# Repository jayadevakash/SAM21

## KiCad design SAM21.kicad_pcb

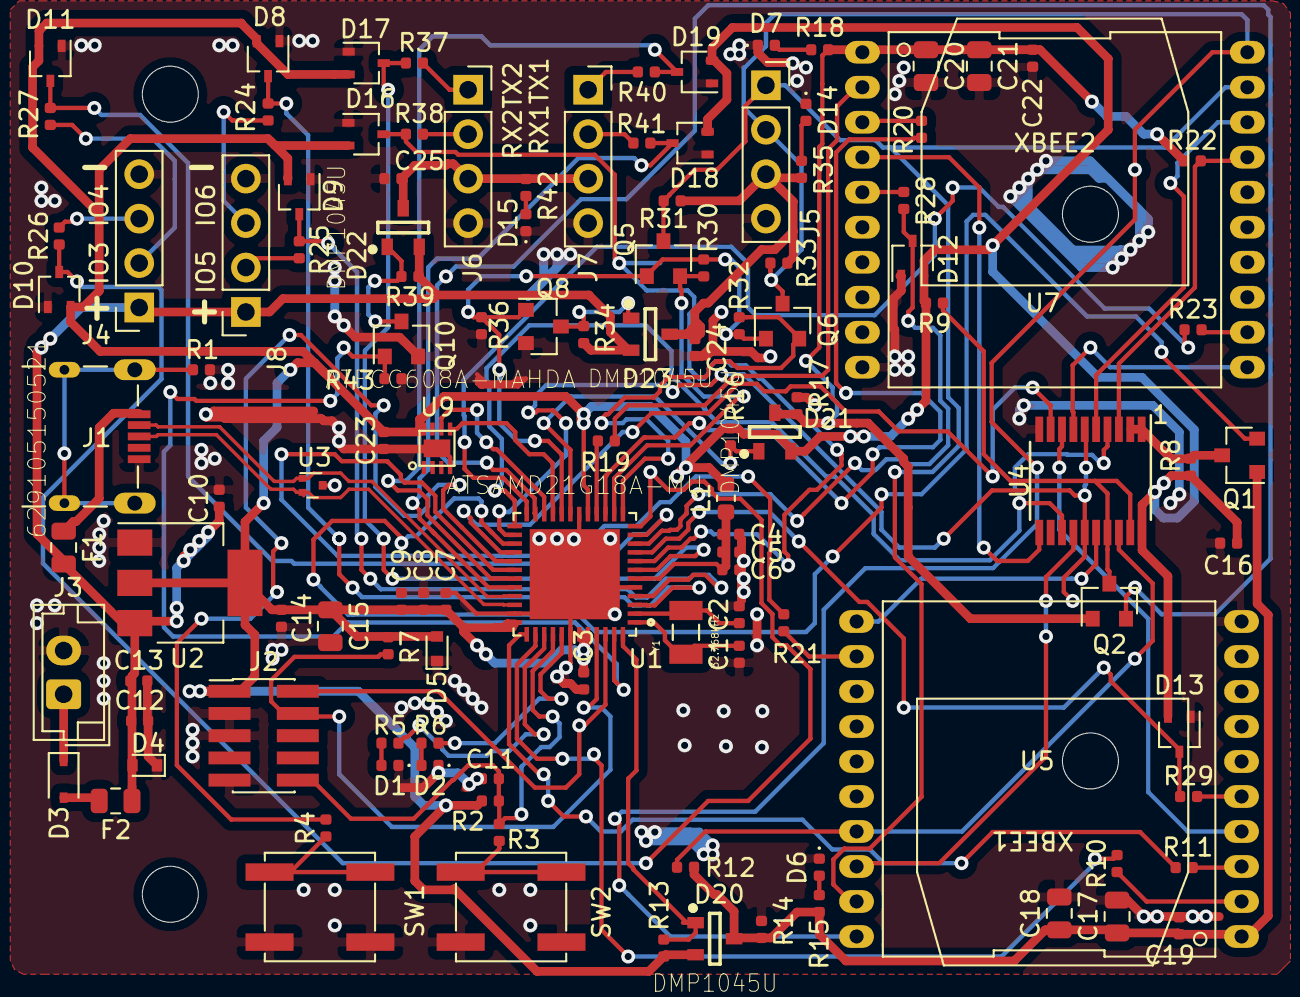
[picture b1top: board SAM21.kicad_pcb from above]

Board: 2 copper layers, 122 parts (0 on the bottom side), 89 nets.

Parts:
C1, C2: 12pF; C_0402_1005Metric
C3, C4, C5, C19, C22, C24, C25: 2u2F; C_0402_1005Metric
C6, C7, C8, C9, C10, C11, C12, C13, C14, C16, C23: 100nF; C_0402_1005Metric
C15, C17, C18, C20, C21: 22uF; C_0805_2012Metric
D1, D2, D6, D7, D14, D15: LED; LED_0402_1005Metric
D3: BAS3010; D_SOD-323
D4: ESD5Z5.0T1G; D_SOD-523
D5: ESD5Z3.3T1G; D_SOD-523
D8, D9, D10, D11, D12, D13, D16, D17, D18, D19: D_BAT30S; SOT-323_SC-70
D20, D21, D22, D23: DMP1045U; SOT92P240X110-3N
F1, F2: 0.5A; Fuse_0805_2012Metric
H1, H2, H3, H4: MountingHole; MountingHole_3.2mm_M3
J1: 629105150521; microusb
J2: Conn_ARM_JTAG_SWD_10; PinHeader_2x05_P1.27mm_Vertical_SMD
J3: Conn_01x02_Male; JST_EH_B2B-EH-A_1x02_P2.50mm_Vertical
J4, J5, J6, J7, J8: Conn_01x04_Male; PinSocket_1x04_P2.54mm_Vertical
L1: BLM18PG221SH1D; L_0603_1608Metric
Q1, Q2, Q5, Q6, Q8, Q10: BSS138; SOT-23
R1: 0E; R_0402_1005Metric
R2, R14, R17: 10kE; R_0402_1005Metric
R3, R24, R25, R26, R27, R28, R29, R37, R38, R40, R41: 330E; R_0402_1005Metric
R4, R5, R6, R7, R15, R18, R35, R42: 1kE; R_0402_1005Metric
R8, R9, R12, R13, R16, R22, R34, R36, R39, R43: 100kE; R_0402_1005Metric
R10, R11, R19, R20: 4k7; R_0402_1005Metric
R21, R23, R30, R31, R32, R33: 4k7E; R_0402_1005Metric
SW1, SW2: SW_Push; SW_SPST_EVPBF
U1: ATSAMD21G18A-MU; QFN50P700X700X90-49N
U2: AP1117-33; SOT-223-3_TabPin2
U3: ESD5V3U2U-03F; SOT-723
U4: 74lvc244; TSSOP-20_4.4x6.5mm_P0.65mm
U5, U7: XBEE
U9: ATECC608A-MAHDA; UDFN-8
Y1: 32.768kHz; XTAL_ECS-.327-12.5-34B-TR

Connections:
1A1: Q1.3, R8.1, U4.1, U4.2
#RESET: C11.1, J2.10, R2.2, R3.1, U1.40
+5V: C10.1, C12.1, C13.1, D4.2, D22.2, D23.2, F1.2, F2.1, J4.1, J8.1, R34.1, R39.1, U2.3
D0_SW: R4.2, U1.29
D1_IO13.3B: D13.3, R29.1, U1.9
D2_IO23.3B: D12.3, R28.1, U1.10
D3_IO33.3B: D11.3, R27.1, U1.11
D4_IO43.3B: D10.3, R26.1, U1.12
D5_IO53.3B: D9.3, R25.1, U1.4
D6_IO63.3B: D8.3, R24.1, U1.3
D7_STATUS_RED: R5.2, U1.39
D8_STATUS_GREEN: R6.2, U1.41
D9_UART_PWR3.1D: Q10.1, R43.2, U1.47
D10_TX13.2C: D19.3, R40.1, U1.31
D11_RX13.2C: D18.3, R41.1, U1.32
D12_TX23.3C: D17.3, R37.1, U1.7
D13_RX23.3C: D16.3, R38.1, U1.8
D14_I2C_PWR3.5B: Q5.1, Q6.1, Q8.1, R30.1, R32.1, R36.2, U1.20
D15_SDA3.5B: Q6.2, R32.2, U1.13
D16_SCL3.5B: Q5.2, R30.2, U1.14
D17_SDA_IMU4.3B: U1.21, U9.5
D18_SCL_IMU4.3B: U1.22, U9.6
D19_MOSI2.2A: U1.25, U4.4, U4.13
D20_SCK2.2A: U1.26, U4.6, U4.15
D21_MISO2.3A: U1.28, U4.9
D22_XB1_PWR2.5A: D20.1, R13.2, U1.48
D23_CS_XB12.2A: Q1.2, U1.27
D24_INT_XB12.4B: R21.1, U1.30
D25_TX_XB12.2B: R11.2, U1.37
D26_RX_XB12.2B: R10.2, U1.38
D27_XB2_PWR2.5B: D21.1, R16.2, U1.19
D28_CS_XB22.2C: Q2.2, U1.23
D29_INT_XB22.4D: R23.1, U1.24
D30_TX_XB22.2C: R20.2, U1.15
D31_RX_XB22.2C: R19.2, U1.16
GND: C1.1, C2.2, C3.2, C4.2, C5.2, C6.2, C7.2, C8.2, C9.2, C10.2, C11.2, C12.2, C13.2, C14.2, C15.2, C16.2, C17.2, C18.2, C19.2, C20.2, C21.2, C22.2, C23.2, C24.2, C25.2, D1.1, D2.1, D4.1, D5.1, D6.1, D7.1, D8.1, D9.1, D10.1, D11.1, D12.1, D13.1, D14.1, D15.1, D16.1, D17.1, D18.1, D19.1, J1.5, J2.3, J2.5, J2.9, J3.2, J4.4, J5.4, J6.4, J7.4, J8.4, Q8.2, Q10.2, R1.2, R14.2, R17.2, R36.1, R43.1, SW1.2, SW2.1, U1.5, U1.18, U1.35, U1.42, U1.49, U2.1, U3.3, U4.10, U5.10, U7.10, U9.4, U9.THERM
I2C_SCL: J5.1, Q5.3, R31.2, U5.19, U7.19
I2C_SDA: J5.2, Q6.3, R33.2, U5.20, U7.20
I2C_VCC: C24.1, D23.3, J5.3, R31.1, R33.1, R35.1
IO1: R29.2, U5.5
IO2: R28.2, U7.5
IO3: J4.2, R27.2
IO4: J4.3, R26.2
IO5: J8.2, R25.2
IO6: J8.3, R24.2
unnamed: D1.2, R5.1
unnamed: D2.2, R6.1
unnamed: D3.1, J3.1
unnamed: D3.2, F2.2
unnamed: D6.2, R15.1
unnamed: D7.2, R18.1
unnamed: D14.2, R35.2
unnamed: D15.2, R42.2
unnamed: D22.1, Q10.3, R39.2
unnamed: D23.1, Q8.3, R34.2
unnamed: J1.SHELL, J1.SHELL1, J1.SHELL2, J1.SHELL3, R1.1
unnamed: J6.1, R37.2
unnamed: J6.2, R38.2
unnamed: J7.1, R40.2
unnamed: J7.2, R41.2
unnamed: Q2.3, R9.1, U4.17, U4.19
unnamed: R3.2, SW2.2
unnamed: R4.1, SW1.1
unnamed: R10.1, U5.2
unnamed: R11.1, U5.3
unnamed: R19.1, U7.2
unnamed: R20.1, U7.3
unnamed: R21.2, U5.12
unnamed: R23.2, U7.12
SWCLK: J2.4, R7.1, U1.45
SWDIO: J2.2, U1.46
UART_VCC: C25.1, D22.3, J6.3, J7.3, R42.1
USB_D_N: J1.2, U1.33, U3.1
USB_D_P: J1.3, U1.34, U3.2
VBUS: F1.1, J1.1
VDDANA: C4.1, C5.1, C6.1, L1.1, U1.6
VDDCORE: C3.1, C7.1, C8.1, C9.1, C14.1, C15.1, C16.1, C23.1, D5.2, D8.2, D9.2, D10.2, D11.2, D12.2, D13.2, D16.2, D17.2, D18.2, D19.2, D20.2, D21.2, J2.1, L1.2, R2.1, R7.2, R8.2, R9.2, R13.1, R16.1, U1.17, U1.36, U1.43, U1.44, U2.2, U4.20, U9.8
XB1_CS: R12.2, U4.18, U5.17
XB1_MISO: U4.8, U5.4
XB1_MOSI: U4.16, U5.11
XB1_SCK: U4.14, U5.18
XB1_VCC: C17.1, C18.1, C19.1, D20.3, Q1.1, R12.1, R14.1, R15.2, U5.1
XB2_CS: R22.2, U4.3, U7.17
XB2_MISO: U4.11, U7.4
XB2_MOSI: U4.7, U7.11
XB2_SCK: U4.5, U7.18
XB2_VCC: C20.1, C21.1, C22.1, D21.3, Q2.1, R17.1, R18.2, R22.1, U7.1
XTAL1: C1.2, U1.1, Y1.1
XTAL2: C2.1, U1.2, Y1.2

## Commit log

2019-08-18 Fixed some Errors
2019-08-19 Fixed One Exception
